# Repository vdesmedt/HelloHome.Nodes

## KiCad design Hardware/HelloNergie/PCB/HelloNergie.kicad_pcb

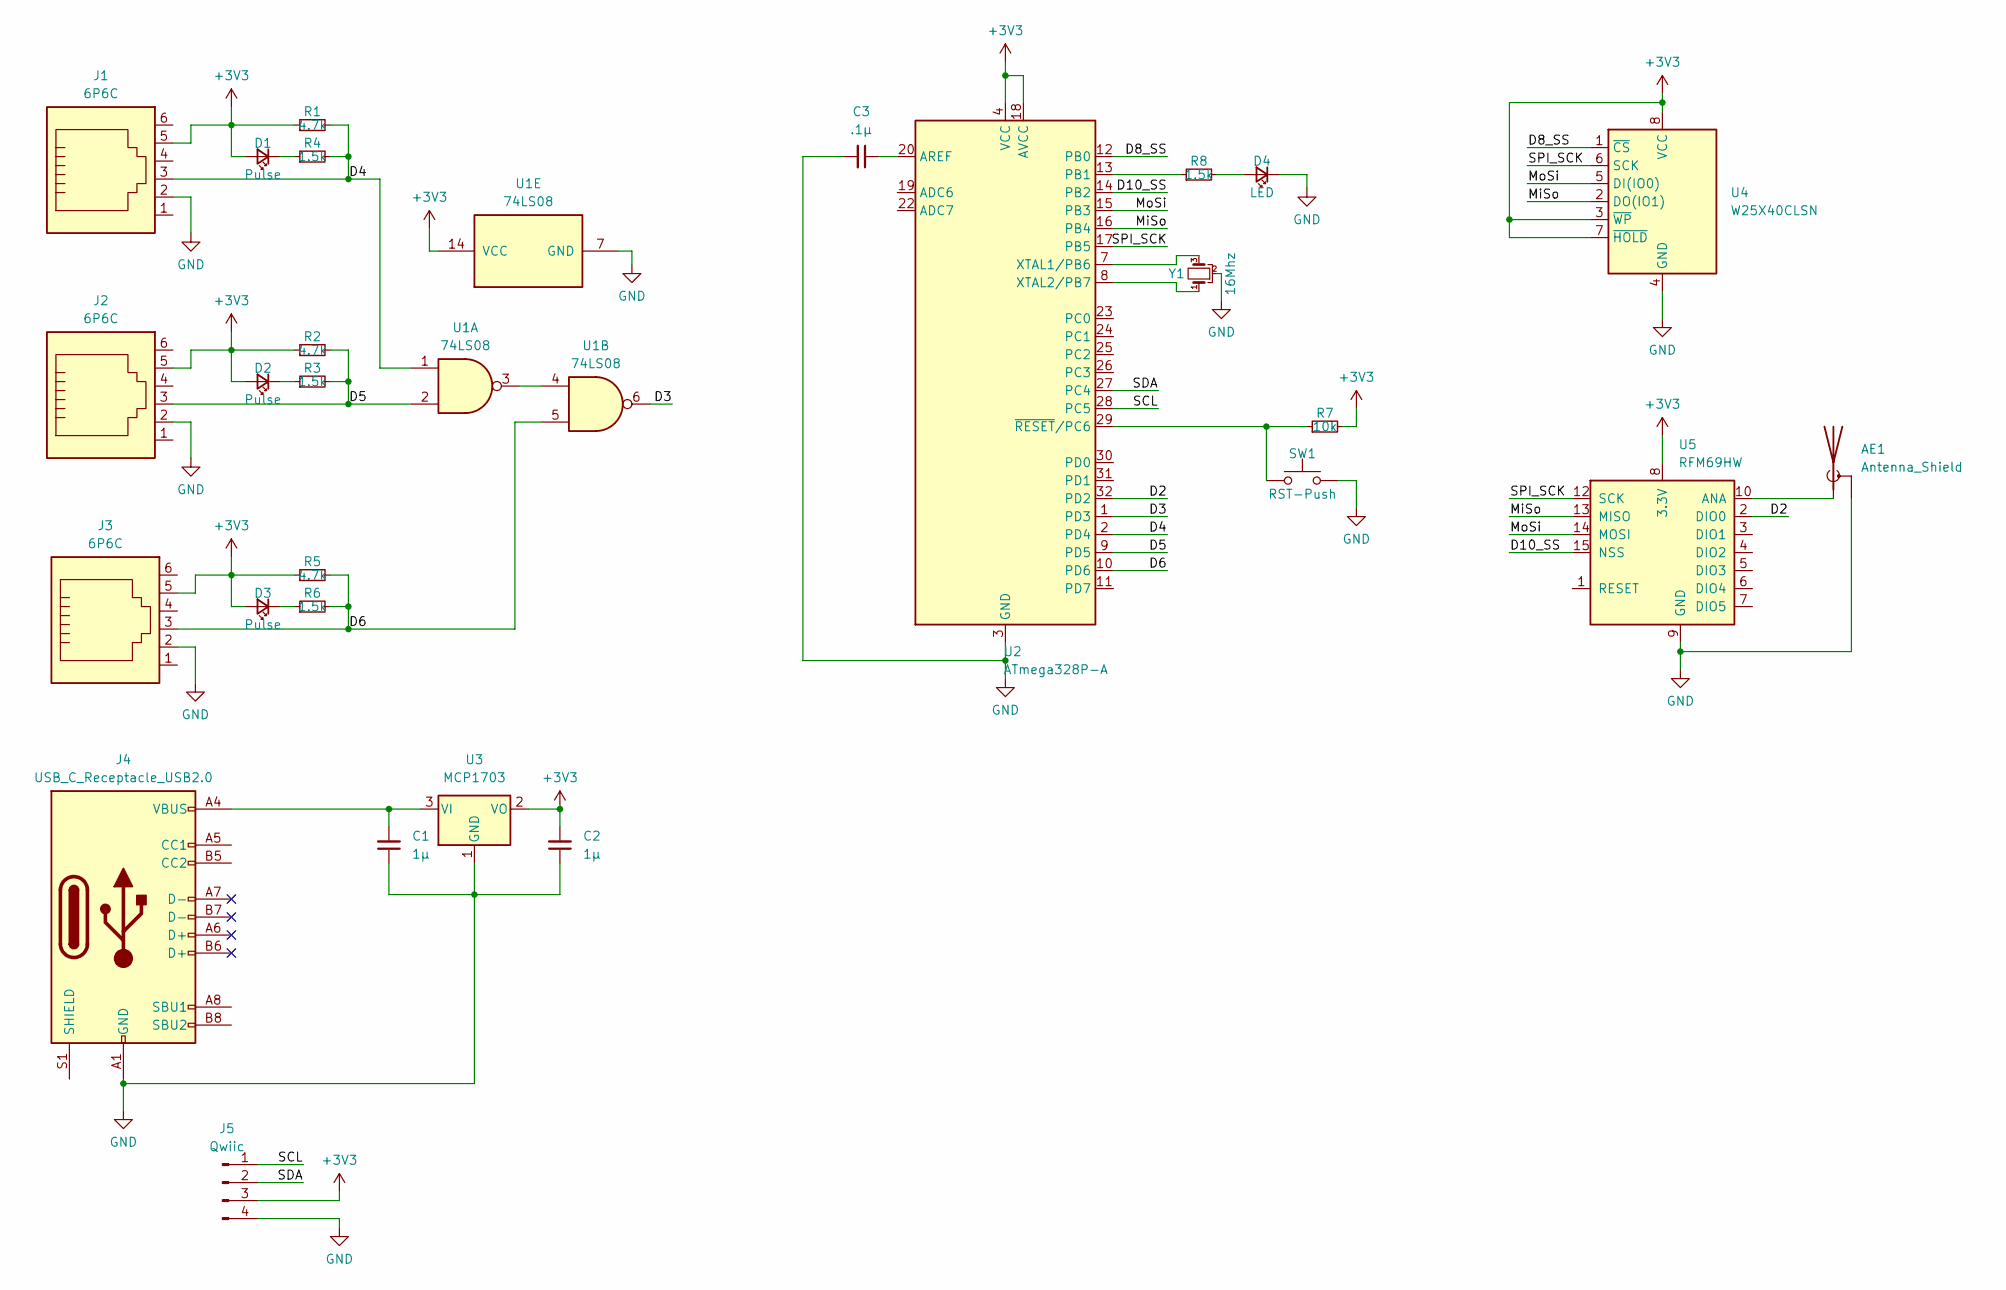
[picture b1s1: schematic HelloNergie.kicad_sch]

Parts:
AE1: Antenna_Shield; U.FL_Molex_MCRF_73412-0110_Vertical
C1, C2: 1µ; C_0805_2012Metric_Pad1.18x1.45mm_HandSolder
C3: .1µ; C_0805_2012Metric_Pad1.18x1.45mm_HandSolder
D1, D2, D3: Pulse; LED_0805_2012Metric_Pad1.15x1.40mm_HandSolder
D4: LED; LED_0805_2012Metric_Pad1.15x1.40mm_HandSolder
J1, J2, J3: 6P6C; RJ12_Amphenol_54601-x06_Horizontal
J4: USB_C_Receptacle_USB2.0; USB_C_Receptacle_GCT_USB4085
J5: Qwiic; JST_SH_SM04B-SRSS-TB_1x04-1MP_P1.00mm_Horizontal
R1, R2, R5: 4.7k; R_0805_2012Metric_Pad1.20x1.40mm_HandSolder
R3, R4, R6, R8: 1.5k; R_0805_2012Metric_Pad1.20x1.40mm_HandSolder
R7: 10k; R_0805_2012Metric_Pad1.20x1.40mm_HandSolder
SW1: RST-Push; SW_Tactile_SPST_NO_Straight_CK_PTS636Sx25SMTRLFS
U1: 74LS08; SOIC-14_3.9x8.7mm_P1.27mm
U2: ATmega328P-A; TQFP-32_7x7mm_P0.8mm
U3: MCP1703; SOT-23
U4: W25X40CLSN; SOIC-8_3.9x4.9mm_P1.27mm
U5: RFM69HW; HOPERF_RFM9XW_SMD
Y1: 16Mhz; Resonator_SMD_Murata_CSTxExxV-3Pin_3.0x1.1mm_HandSoldering

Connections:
+3V3: C2.2, D1.2 (A), D2.2 (A), D3.2 (A), J1.5, J2.5, J3.5, J5.3, R1.1, R2.1, R5.1, R7.2, U1.14 (VCC), U2.4 (VCC), U2.6 (VCC), U2.18 (AVCC), U3.2 (VO), U4.3 (~WP), U4.7 (~HOLD), U4.8 (VCC), U5.8 (3.3V)
/D2: U2.32 (PD2), U5.2 (DIO0)
/D3: U1.6, U2.1 (PD3)
/D4: J1.3, R1.2, R4.2, U1.1, U2.2 (PD4)
/D5: J2.3, R2.2, R3.2, U1.2, U2.9 (PD5)
/D6: J3.3, R5.2, R6.2, U1.5, U2.10 (PD6)
/D8_SS: U2.12 (PB0), U4.1 (~CS)
/D10_SS: U2.14 (PB2), U5.15 (NSS)
/MiSo: U2.16 (PB4), U4.2 (DO(IO1)), U5.13 (MISO)
/MoSi: U2.15 (PB3), U4.5 (DI(IO0)), U5.14 (MOSI)
/SCL: J5.1, U2.28 (PC5)
/SDA: J5.2, U2.27 (PC4)
/SPI_SCK: U2.17 (PB5), U4.6 (SCK), U5.12 (SCK)
GND: AE1.2 (Shield), C1.1, C2.1, C3.2, D4.1 (K), J1.2, J2.2, J3.2, J4.A1 (GND), J4.A12 (GND), J4.B1 (GND), J4.B12 (GND), J5.4, SW1.2, U1.7 (GND), U2.3 (GND), U2.5 (GND), U2.21 (GND), U3.1 (GND), U4.4 (GND), U5.9 (GND), U5.11 (GND), Y1.2
unnamed: AE1.1 (A), U5.10 (ANA)
unnamed: D1.1 (K), R4.1
unnamed: D2.1 (K), R3.1
unnamed: D3.1 (K), R6.1
unnamed: D4.2 (A), R8.2
unnamed: U1.3, U1.4
unnamed: C3.1, U2.20 (AREF)
unnamed: R8.1, U2.13 (PB1)
unnamed: U2.7 (XTAL1/PB6), Y1.3
unnamed: U2.8 (XTAL2/PB7), Y1.1
unnamed: R7.1, SW1.1, U2.29 (~RESET/PC6)
unnamed: C1.2, J4.A4 (VBUS), J4.A9 (VBUS), J4.B4 (VBUS), J4.B9 (VBUS), U3.3 (VI)

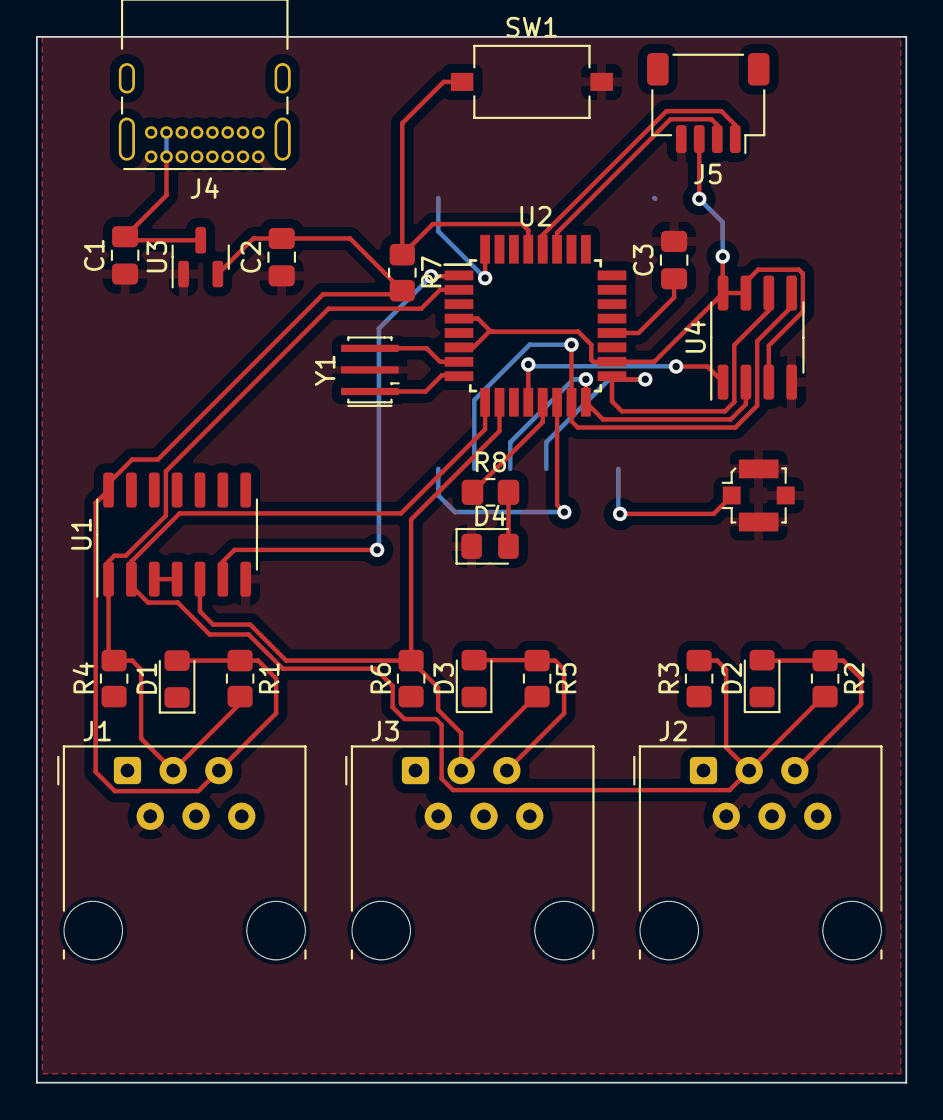
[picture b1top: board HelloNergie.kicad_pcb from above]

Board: 2 copper layers, 48.3 x 58.1 mm, 28 parts (1 on the bottom side), 26 nets.

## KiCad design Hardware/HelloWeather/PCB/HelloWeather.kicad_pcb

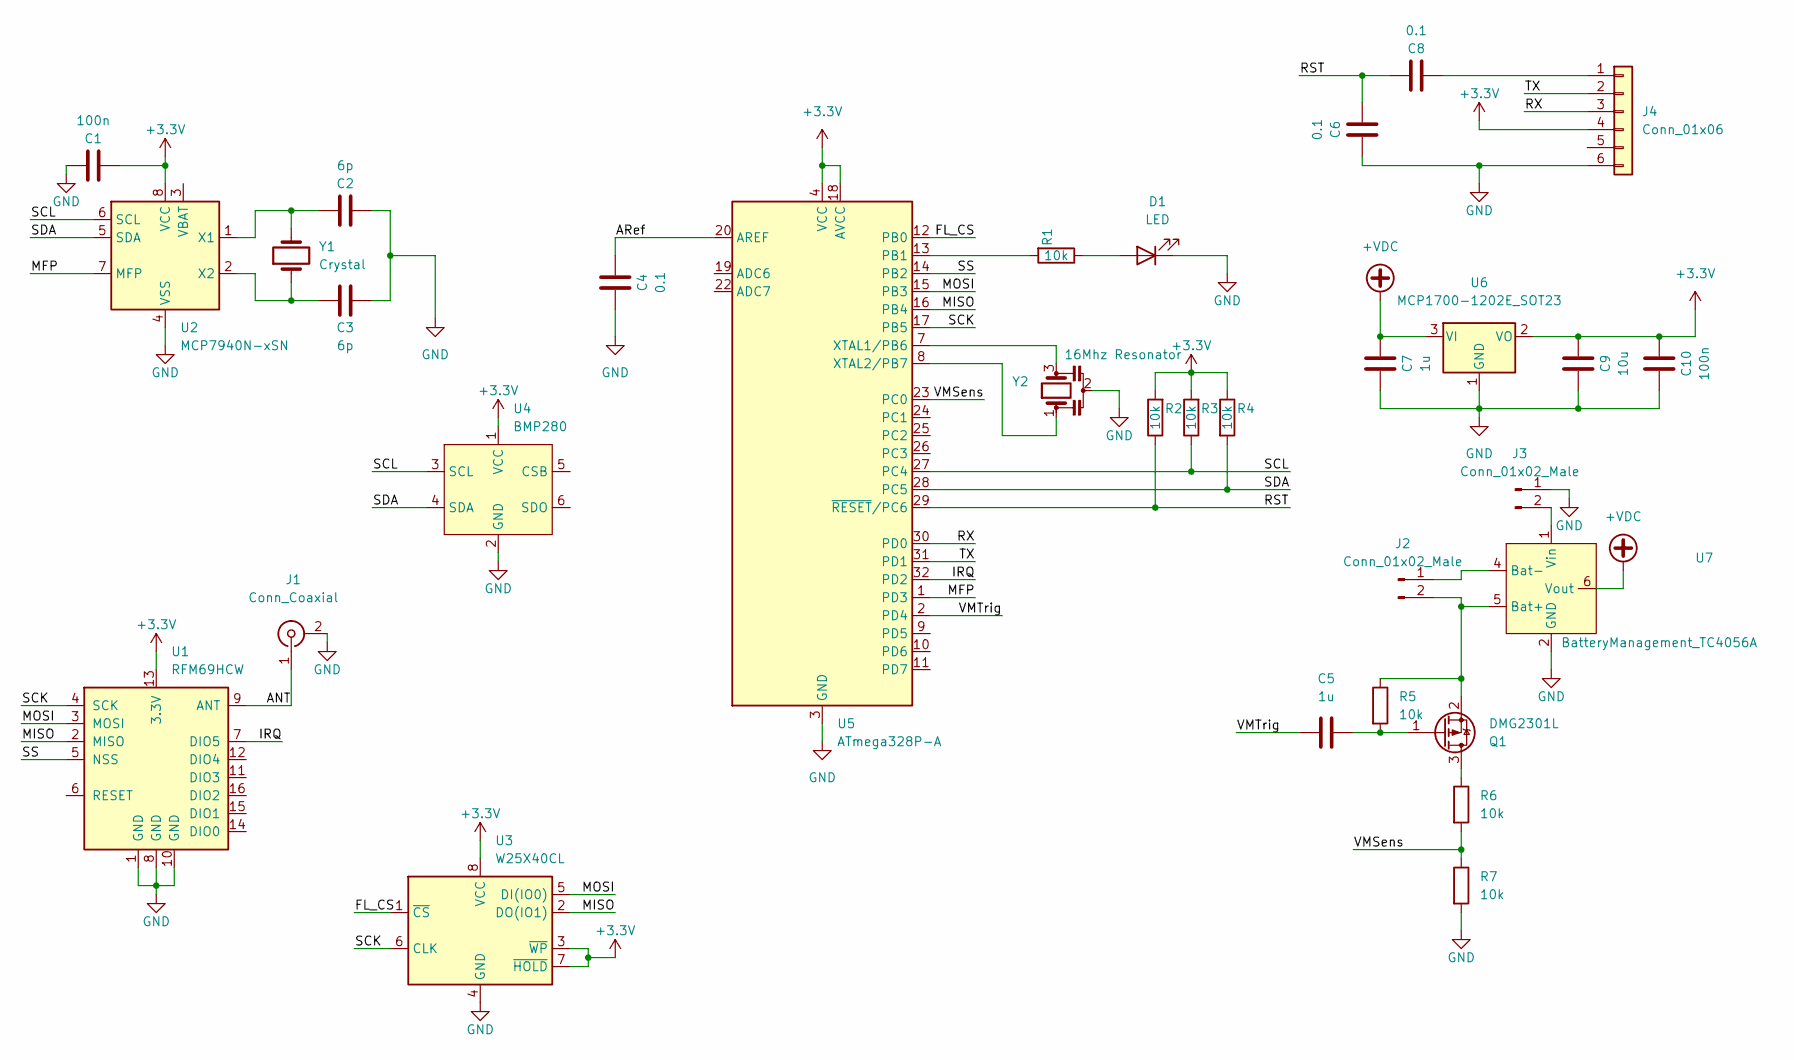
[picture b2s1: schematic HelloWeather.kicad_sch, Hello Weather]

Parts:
C1, C10: 100n; C_0805_2012Metric_Pad1.18x1.45mm_HandSolder
C2, C3: 6p; C_0805_2012Metric_Pad1.18x1.45mm_HandSolder
C4, C6, C8: 0.1; C_0805_2012Metric_Pad1.18x1.45mm_HandSolder
C5, C7: 1u; C_0805_2012Metric_Pad1.18x1.45mm_HandSolder
C9: 10u; C_0805_2012Metric_Pad1.18x1.45mm_HandSolder
D1: LED; LED_0805_2012Metric_Pad1.15x1.40mm_HandSolder
J1: Conn_Coaxial; U.FL_Molex_MCRF_73412-0110_Vertical
J2, J3: Conn_01x02_Male; JST_XH_B2B-XH-A_1x02_P2.50mm_Vertical
J4: Conn_01x06; PinHeader_1x06_P2.54mm_Vertical
Q1: DMG2301L; SOT-23
R1, R2, R3, R4, R5, R6, R7: 10k; R_0805_2012Metric_Pad1.20x1.40mm_HandSolder
U1: RFM69HCW; HOPERF_RFM9XW_SMD
U2: MCP7940N-xSN; SOIC-8_3.9x4.9mm_P1.27mm
U3: W25X40CL; SOIC-8_3.9x4.9mm_P1.27mm
U4: BMP280; BMP280_Breakboard
U5: ATmega328P-A; TQFP-32_7x7mm_P0.8mm
U6: MCP1700-1202E_SOT23; SOT-23_Handsoldering
U7: BatteryManagement_TC4056A; BattMngmnt_TC4056A
Y1: Crystal; Crystal_SMD_EuroQuartz_EQ161-2Pin_3.2x1.5mm_HandSoldering
Y2: 16Mhz Resonator; Resonator_SMD_Murata_CSTxExxV-3Pin_3.0x1.1mm_HandSoldering

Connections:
+3V3: C1.1, C9.2, C10.2, J4.4, R2.2, R3.2, R4.1, U1.13 (3.3V), U2.8 (VCC), U3.3 (~WP), U3.7 (~HOLD), U3.8 (VCC), U4.1 (VCC), U5.4 (VCC), U5.6 (VCC), U5.18 (AVCC), U6.2 (VO)
+VDC: C7.2, U6.3 (VI), U7.6 (Vout)
/ANT: J1.1 (In), U1.9 (ANT)
/ARef: C4.2, U5.20 (AREF)
/FL_CS: U3.1 (~CS), U5.12 (PB0)
/IRQ: U1.7 (DIO5), U5.32 (PD2)
/MFP: U2.7 (MFP), U5.1 (PD3)
/MISO: U1.2 (MISO), U3.2 (DO(IO1)), U5.16 (PB4)
/MOSI: U1.3 (MOSI), U3.5 (DI(IO0)), U5.15 (PB3)
/RST: C6.1, C8.2, R2.1, U5.29 (~RESET/PC6)
/RX: J4.3, U5.30 (PD0)
/SCK: U1.4 (SCK), U3.6 (CLK), U5.17 (PB5)
/SCL: R3.1, U2.6 (SCL), U4.3 (SCL), U5.27 (PC4)
/SDA: R4.2, U2.5 (SDA), U4.4 (SDA), U5.28 (PC5)
/SS: U1.5 (NSS), U5.14 (PB2)
/TX: J4.2, U5.31 (PD1)
/VMSens: R6.2, R7.1, U5.23 (PC0)
/VMTrig: C5.1, U5.2 (PD4)
GND: C1.2, C2.2, C3.2, C4.1, C6.2, C7.1, C9.1, C10.1, D1.1 (K), J1.2 (Ext), J3.1, J4.6, R7.2, U1.1 (GND), U1.8 (GND), U1.10 (GND), U2.4 (VSS), U3.4 (GND), U4.2 (GND), U5.3 (GND), U5.5 (GND), U5.21 (GND), U6.1 (GND), U7.2 (GND), Y2.2
unnamed: D1.2 (A), R1.1
unnamed: J2.1, U7.4 (Bat-)
unnamed: J2.2, Q1.2 (S), R5.1, U7.5 (Bat+)
unnamed: J3.2, U7.1 (Vin)
unnamed: C8.1, J4.1
unnamed: Q1.3 (D), R6.1
unnamed: C5.2, Q1.1 (G), R5.2
unnamed: C2.1, U2.1 (X1), Y1.2
unnamed: C3.1, U2.2 (X2), Y1.1
unnamed: R1.2, U5.13 (PB1)
unnamed: U5.7 (XTAL1/PB6), Y2.3
unnamed: U5.8 (XTAL2/PB7), Y2.1

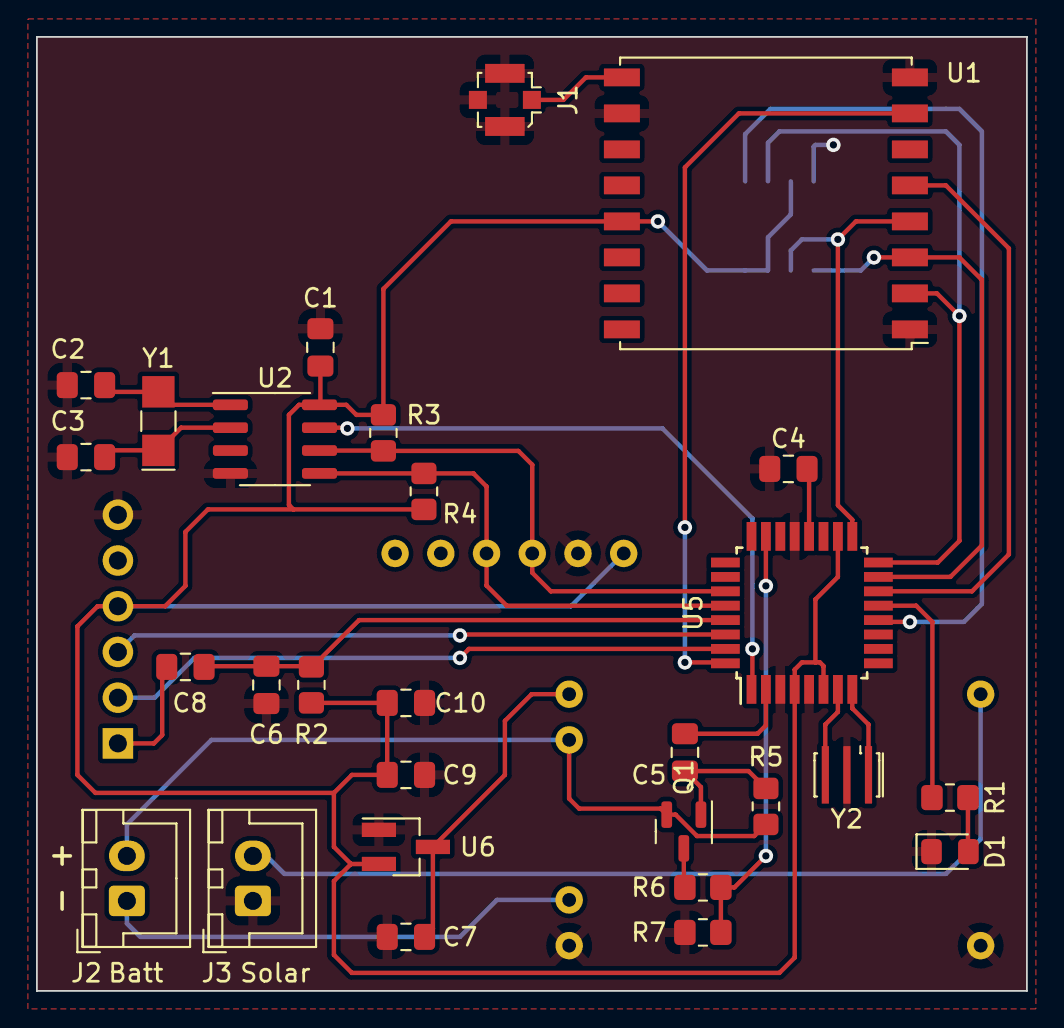
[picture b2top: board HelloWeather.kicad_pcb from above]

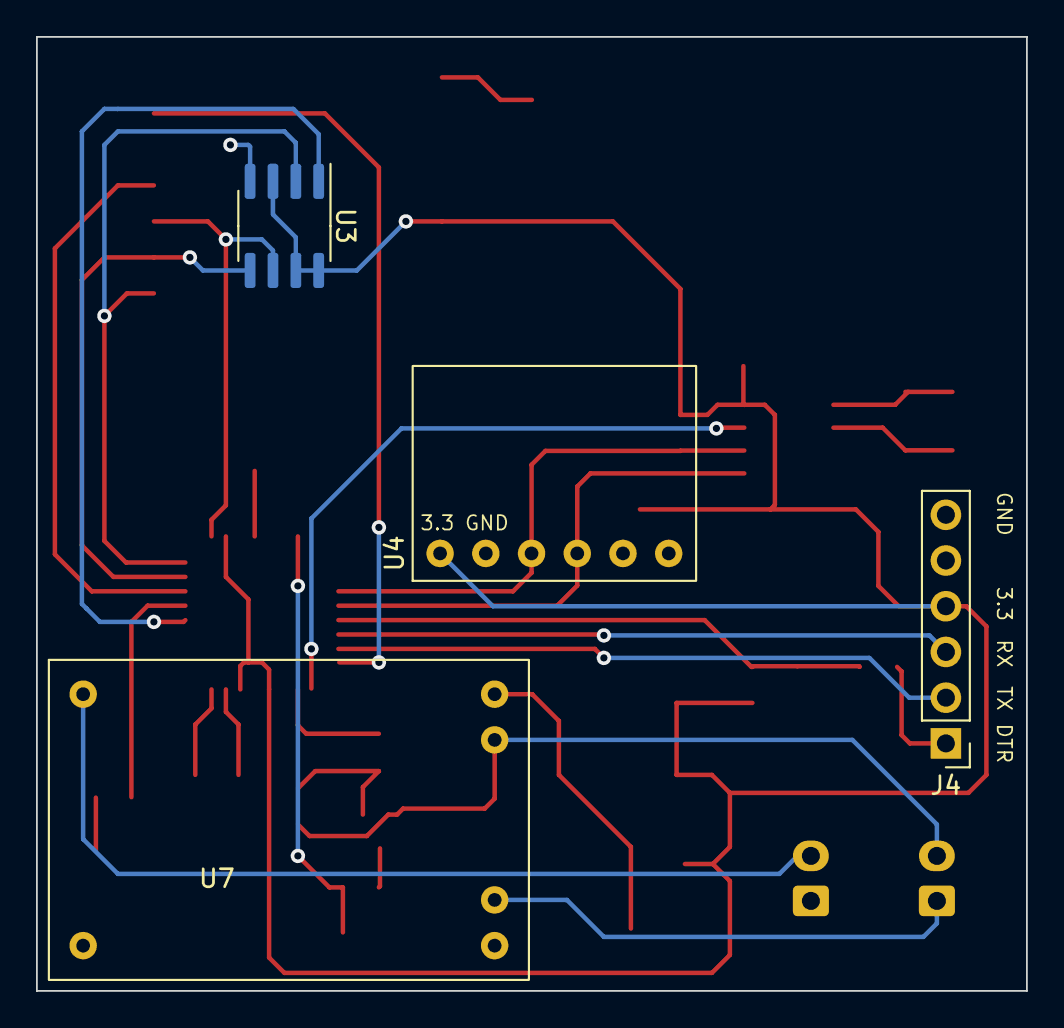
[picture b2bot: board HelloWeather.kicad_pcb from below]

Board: 2 copper layers, 55.0 x 53.0 mm, 32 parts (4 on the bottom side), 31 nets.

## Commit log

2017-12-30 first line of code
2017-12-30 travid-deploy
2017-12-30 deploy tag
2017-12-30 blinking
2017-12-30 versioning
2017-12-30 add RFM92 lib
2017-12-31 Custom hex filename for travis deploy
2018-01-14 First basic working version
2018-01-27 Include WirelessHEX69
2018-01-27 Re order report & command
2018-01-27 Added RestartCommand
2018-01-27 Handle RestartCommand
2018-09-24 Migrated to VSCode
2018-09-25 Move message and version to lib
2018-09-25 Fix CI after version.h move to lib
2018-10-01 Changed config handling
2018-10-19 Started on linux
2019-11-30 New PIO (Deps)
2019-12-02 Updated FTDI Name
2019-12-02 NodeId on 10bits
2019-12-02 SendAck even if NodeConfig has not right size
2019-12-07 Lot of things :(
2019-12-07 Update Travis CI
2019-12-07 Travis Fix
2019-12-08 Fix includes
2019-12-08 remove .vscode
2019-12-08 gitignore
2019-12-09 Adapt travis
2020-10-25 Bunch of updates :(
2020-10-25 Merging RFM2Pi
2020-10-25 Merging HellNergie
2020-10-25 Merging OTA
2020-10-25 Adding other nodes & SharedLib
2020-10-25 Code Workspace
2020-10-30 Update RFM2Pi with Cmd Name
2020-10-30 Timeout on HHCentral.Connect
2020-10-30 Prettier
2020-11-02 Updates ;)
2020-11-29 RFM Config at start
2021-11-28 Fix build warnings
2021-11-28 Expose Features
2021-11-28 PIO Internals
2021-11-28 Update lib includes
2021-11-28 Setup basic node
2021-11-28 Fix shared libaries references
2021-12-03 Update OTA to latest version
2021-12-03 Added MsgId
2021-12-04 Uses HighPower on OTA Pogrammer
2021-12-04 Added PingCommand
2021-12-04 Use Git Hash as Version
2021-12-04 added hhgtw env for RFM2Pi
2021-12-04 Git FLAG as Version
2021-12-04 Send returns HHCErr_SentFailed when failing
2021-12-04 Set upload speed
2021-12-28 RFM2Pi HeartBeat
2021-12-28 Log ACK
2021-12-28 Only send pulse every x Minutes
2022-01-04 Added NodeConfigurator Project
2022-01-05 Add BME280 for Environment Readings
2022-01-15 SendVAReport
2022-01-15 Send VAReport
2022-01-15 Sleep radio after send
2022-01-15 No longer need Version.h
2022-01-22 Sleep Flash
2022-02-02 Starting register based impementation of config
2022-02-02 Adding I2C Scanner
2022-02-02 Comment
2022-02-02 Generic Send method
2022-02-18 HelloWeather added
2022-02-19 Weather Folder change
2022-02-20 Added ControllerComand & Response
2022-02-20 Updated path + Loggn Changes
2022-02-20 Several updates to logging & send data
2023-12-04 Change how report size is calculated vs provided
2023-12-04 SharedLibrary structure
2023-12-04 include avr (Intellisense warning on PGM_)
2023-12-05 Comments
2023-12-05 Folder Reorganisation
2023-12-05 Only save registers to flash when dirty
2023-12-05 features, envReport & nodeInfo freq in registers
2023-12-05 Adapt dependencies to Core (symlinc)
2023-12-05 4 Pulse Inputs - no longer use features
2023-12-06 Rename NodInfo & EnvReport period fregister
2023-12-06 Individual register dirtyness
2023-12-06 Individual Register dirtyness commenting
2023-12-06 enum -> typedef enum
